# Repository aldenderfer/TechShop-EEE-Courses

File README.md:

# TechShop EEE Courses
Designed and written by Kristof Aldenderfer, Sam Brown, and Luca Angeleri.

All packets are current as of 04 May 2016. **Do not distribute until all courses are listed as complete.**

Course | Status | Hours | Materials cost | Prerequisite | Notes
--- | --- | --- | --- | --- | ---
Basic Electronics | **Complete** | 3 |  $20 | None | Requirement for all other EEE courses
Circuit Basics: DC | **Complete** | 2 | ? | Basic Electronics | -
Circuit Basics: AC | Alpha | 2 | ? | Circuit Basics: DC | -
Circuit Design with EAGLE | **Complete** | 2.5 | $0 | Circuit Basics: AC | -
PCB Milling with the Othermill | **Complete** | 2 | $5 | Circuit Design with EAGLE | -
Assemble an Arduino | **Complete** | 3 |  $29 | Basic Electronics | -
Arduino Robotics Camp | **Complete** | weeklong | $100 | none (incorporates Basic Electronics) | -

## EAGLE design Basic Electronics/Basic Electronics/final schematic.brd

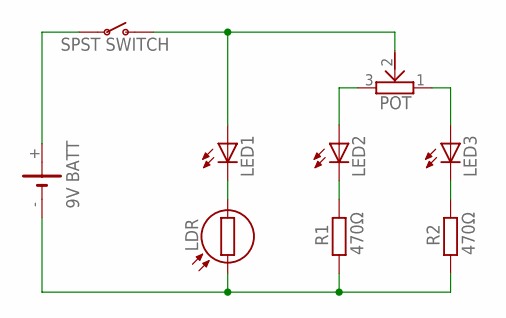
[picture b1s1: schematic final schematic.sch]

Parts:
G1: BATT_9V; 9V_CONNECTOR
LDR: LDR_THRU; LDR
LED1, LED2, LED3: LED5MM
POT: POTENTIOMETER_THRU
R1, R2: 470Ω; 0207/10
U1: SWITCH-SPST-2TV; SWITCH-SPST-VERTICAL

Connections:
unnamed: G1.-, LDR.1, R1.1, R2.1
unnamed: LED1.A, POT.2, U1.1 (O)
unnamed: LDR.2, LED1.K (C)
unnamed: LED3.K (C), R2.2
unnamed: LED3.A, POT.1
unnamed: LED2.A, POT.3
unnamed: G1.+, U1.2
unnamed: LED2.K (C), R1.2

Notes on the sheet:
9V BATT
SPST SWITCH

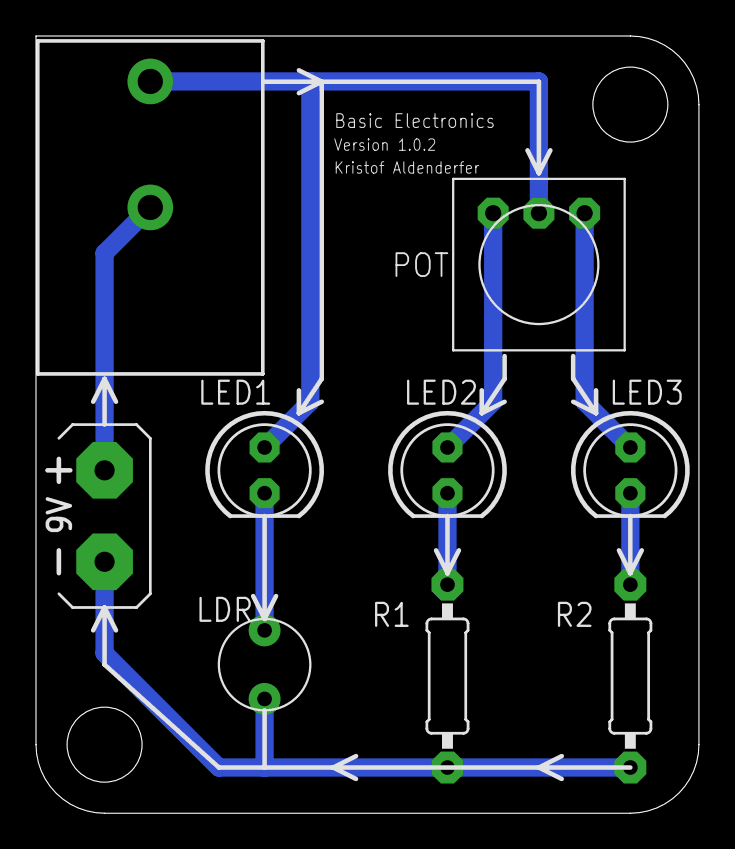
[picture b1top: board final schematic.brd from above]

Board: 2 copper layers, 36.8 x 43.2 mm, 9 parts (0 on the bottom side), 8 nets.

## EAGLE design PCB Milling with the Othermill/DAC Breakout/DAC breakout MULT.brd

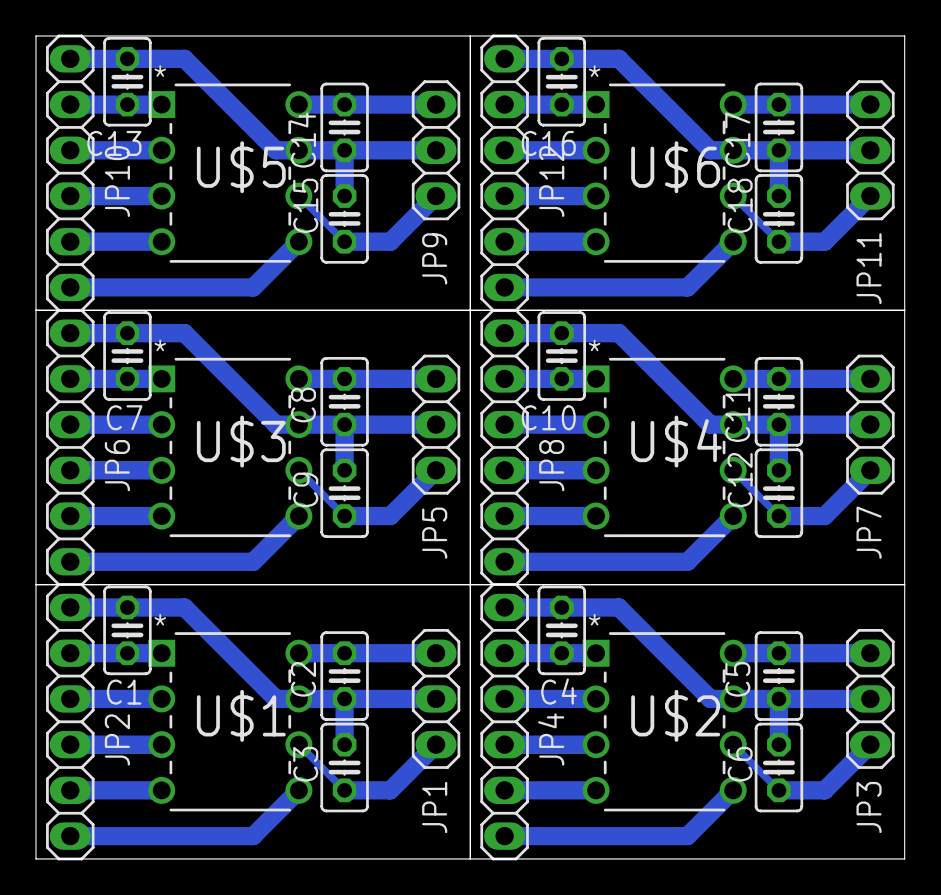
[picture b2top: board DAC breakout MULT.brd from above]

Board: 2 copper layers, 48.3 x 45.7 mm, 36 parts (0 on the bottom side), 48 nets.

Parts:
C1, C4, C7, C10, C13, C16: 0.1uF; C025-025X050
C2, C3, C5, C6, C8, C9, C11, C12, C14, C15, C17, C18: 1uF; C025-025X050
JP1, JP3, JP5, JP7, JP9, JP11: 1X03
JP2, JP4, JP6, JP8, JP10, JP12: 1X06
U$1, U$2, U$3, U$4, U$5, U$6: MCP4822-E/P; DIP254P762X432-8

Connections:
GND: C1.2, C2.2, C3.2, JP1.2, JP2.6, U$1.7
GND1: C4.2, C5.2, C6.2, JP3.2, JP4.6, U$2.7
GND2: C7.2, C8.2, C9.2, JP5.2, JP6.6, U$3.7
GND3: C10.2, C11.2, C12.2, JP7.2, JP8.6, U$4.7
GND4: C13.2, C14.2, C15.2, JP9.2, JP10.6, U$5.7
GND5: C16.2, C17.2, C18.2, JP11.2, JP12.6, U$6.7
unnamed: C1.1, JP2.5, U$1.1
unnamed: C2.1, JP1.1, U$1.8
unnamed: C3.1, JP1.3, U$1.6
unnamed: JP2.4, U$1.2
unnamed: JP2.3, U$1.3
unnamed: JP2.2, U$1.4
unnamed: JP2.1, U$1.5
unnamed: C4.1, JP4.5, U$2.1
unnamed: JP4.4, U$2.2
unnamed: JP4.3, U$2.3
unnamed: JP4.2, U$2.4
unnamed: JP4.1, U$2.5
unnamed: C5.1, JP3.1, U$2.8
unnamed: C6.1, JP3.3, U$2.6
unnamed: C7.1, JP6.5, U$3.1
unnamed: JP6.4, U$3.2
unnamed: JP6.3, U$3.3
unnamed: JP6.2, U$3.4
unnamed: JP6.1, U$3.5
unnamed: C8.1, JP5.1, U$3.8
unnamed: C9.1, JP5.3, U$3.6
unnamed: C10.1, JP8.5, U$4.1
unnamed: JP8.4, U$4.2
unnamed: JP8.3, U$4.3
unnamed: JP8.2, U$4.4
unnamed: JP8.1, U$4.5
unnamed: C11.1, JP7.1, U$4.8
unnamed: C12.1, JP7.3, U$4.6
unnamed: C13.1, JP10.5, U$5.1
unnamed: JP10.4, U$5.2
unnamed: JP10.3, U$5.3
unnamed: JP10.2, U$5.4
unnamed: JP10.1, U$5.5
unnamed: C14.1, JP9.1, U$5.8
unnamed: C15.1, JP9.3, U$5.6
unnamed: C16.1, JP12.5, U$6.1
unnamed: JP12.4, U$6.2
unnamed: JP12.3, U$6.3
unnamed: JP12.2, U$6.4
unnamed: JP12.1, U$6.5
unnamed: C17.1, JP11.1, U$6.8
unnamed: C18.1, JP11.3, U$6.6

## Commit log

2015-07-10 :confetti_ball: Added .gitattributes & .gitignore files
2015-07-10 first commit
    v0.1
2015-07-10 0.2
    minor fix, ready for students if necessary
2015-07-13 v0.3
    corrected L/R problem, added test code
2015-07-13 v0.4
    super duper cleanup
2015-07-15 v0.9
    merged luca's PS3 code, general cleanup
2015-07-23 0.9.1
    pinout fix
2015-07-24 0.9.2
    merged ps3 and xboxone
2015-08-21 ABleTank update
    First push of ABleTank code, to be used with Adafruit Bluefruit UART
    friend.
    Red Orm now deprecated.
2015-08-21 0.9.2
2015-09-11 0.9.3
    syntax correction for last week of camp
2015-10-13 code cleanup
2015-12-07 :neckbeard: Added .gitattributes & .gitignore files
2015-12-07 add libraries and cam
2015-12-08 added alpha draft plus drus
2016-01-20 modified support files in prep for new board design
2016-01-21 added gerbers, may not work
2016-01-21 added corrected sch and brd
2016-01-21 reorganized files
2016-01-27 added project files
2016-02-02 modified pinout configuration for easier wiring leads
2016-02-11 added gitignore
2016-02-13 updated Robotics Camp folder; fixed directionDemo
2016-02-13 added flowchart
2016-02-13 added all packets with watermark, renamed folders
2016-02-15 renamed Robotics Camp to Arduino Robotics Camp
2016-02-16 Robotics: added schematic, updated course packet, cleaned up directory
2016-02-16 cleaned up directories, fixed gitignore
2016-02-16 Circuit Design: added diagrams ai
2016-02-19 added proper EAGLE project file structure, more drus
2016-02-19 added descriptions and thumbnails for website
2016-03-01 changed footprints to work on Othermill
2016-03-22 modified resistor pad size
2016-03-23 added 6x panel of board design
2016-04-19 fixed diagram
2016-04-28 added activities pdf
2016-04-28 try fix
2016-04-28 re-add pdf
2016-04-30 changed schematic and code
2016-05-04 renamed to reflect learning outcome change
2016-05-04 corrected schematics; updated readme
2016-05-04 README.md edited online with Bitbucket
2016-05-18 added gearbox mounting holes
2016-05-25 fixed diagrams
2016-05-25 finalized 3 packets and removed watermark
2016-05-25 removed mult board
2016-05-25 removed old packets
